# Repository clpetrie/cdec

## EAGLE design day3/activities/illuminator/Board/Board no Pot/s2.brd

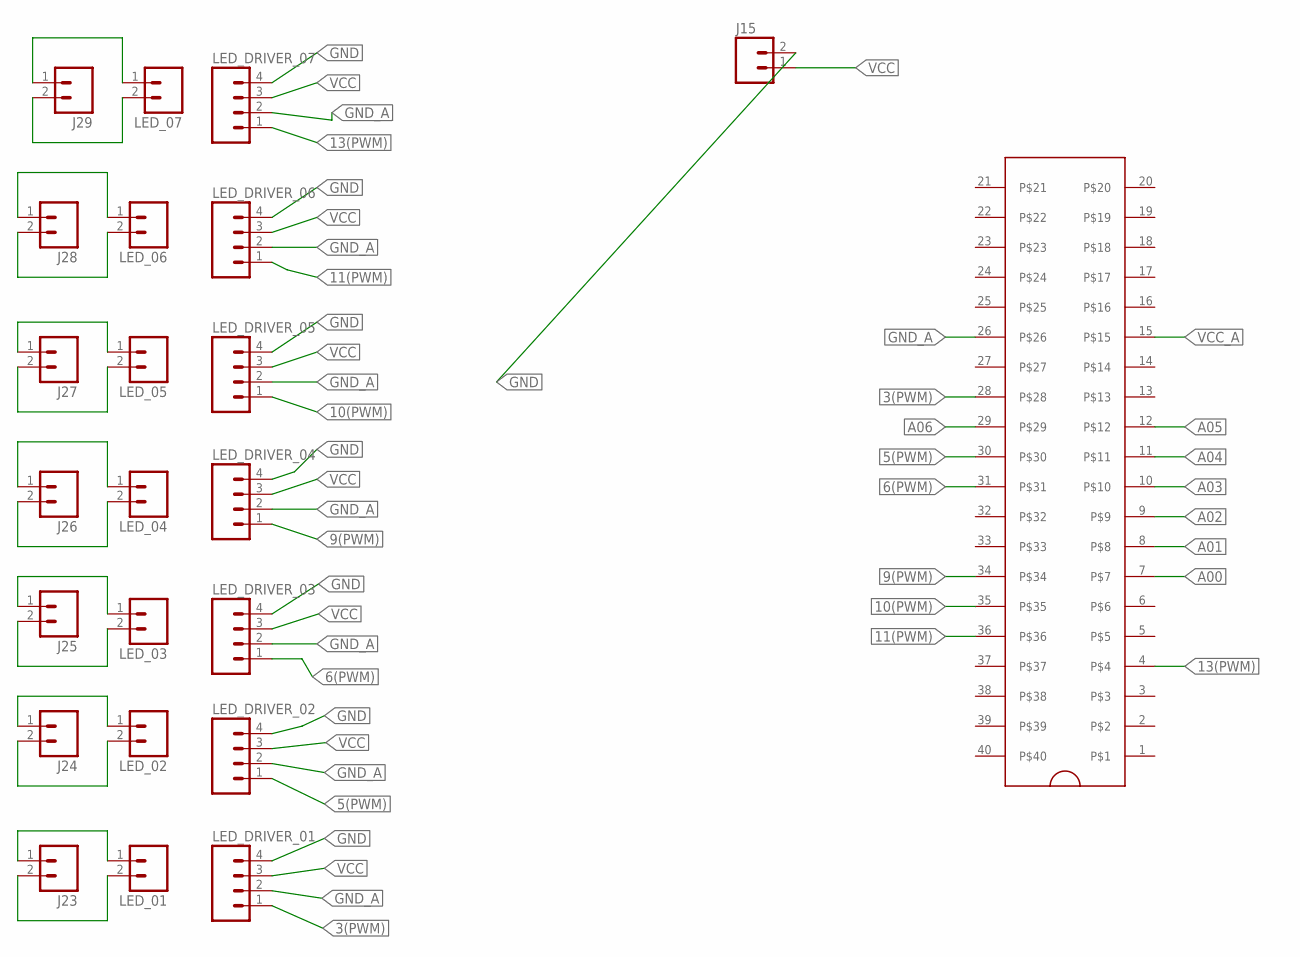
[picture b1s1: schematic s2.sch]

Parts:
ARDUINO_MICRO: ZIFSOCKET-40-6DIL40-6-ZIF_SOCKET; DIL40-6-ZIF_SOCKET
J15, J23, J24, J25, J26, J27, J28, J29: M02PTH; 1X02
LED_01, LED_02, LED_03, LED_04, LED_05, LED_06, LED_07: M02PTH; 1X02
LED_DRIVER_01, LED_DRIVER_02, LED_DRIVER_03, LED_DRIVER_04, LED_DRIVER_05, LED_DRIVER_06, LED_DRIVER_07: M04PTH; 1X04

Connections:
3(PWM): ARDUINO_MICRO.28, LED_DRIVER_01.1
5(PWM): ARDUINO_MICRO.30, LED_DRIVER_02.1
6(PWM): ARDUINO_MICRO.31, LED_DRIVER_03.1
9(PWM): ARDUINO_MICRO.34, LED_DRIVER_04.1
10(PWM): ARDUINO_MICRO.35, LED_DRIVER_05.1
11(PWM): ARDUINO_MICRO.36, LED_DRIVER_06.1
13(PWM): ARDUINO_MICRO.4, LED_DRIVER_07.1
A00: ARDUINO_MICRO.7
A01: ARDUINO_MICRO.8
A02: ARDUINO_MICRO.9
A03: ARDUINO_MICRO.10
A04: ARDUINO_MICRO.11
A05: ARDUINO_MICRO.12
A06: ARDUINO_MICRO.29
GND: J15.2, LED_DRIVER_01.4, LED_DRIVER_02.4, LED_DRIVER_03.4, LED_DRIVER_04.4, LED_DRIVER_05.4, LED_DRIVER_06.4, LED_DRIVER_07.4
GND_A: ARDUINO_MICRO.26, LED_DRIVER_01.2, LED_DRIVER_02.2, LED_DRIVER_03.2, LED_DRIVER_04.2, LED_DRIVER_05.2, LED_DRIVER_06.2, LED_DRIVER_07.2
unnamed: J23.1, LED_01.1
unnamed: J23.2, LED_01.2
unnamed: J24.2, LED_02.2
unnamed: J24.1, LED_02.1
unnamed: J25.2, LED_03.2
unnamed: J25.1, LED_03.1
unnamed: J26.2, LED_04.2
unnamed: J26.1, LED_04.1
unnamed: J27.2, LED_05.2
unnamed: J27.1, LED_05.1
unnamed: J28.2, LED_06.2
unnamed: J28.1, LED_06.1
unnamed: J29.2, LED_07.2
unnamed: J29.1, LED_07.1
VCC: J15.1, LED_DRIVER_01.3, LED_DRIVER_02.3, LED_DRIVER_03.3, LED_DRIVER_04.3, LED_DRIVER_05.3, LED_DRIVER_06.3, LED_DRIVER_07.3
VCC_A: ARDUINO_MICRO.15

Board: 2 copper layers, 23 parts (23 on the bottom side), 24 nets, no tracks yet.

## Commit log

2017-07-30 Added files for day1 only to test things.
2017-07-30 Added files for most other days.
2017-07-31 Added fix for import issue in anaconda.
2017-07-31 Fixed the fix for the "import" issue.
2017-08-01 Testing the .gitignore file.
2017-08-01 Another change to .gitignore.
2017-08-01 testing
2017-08-01 Fixed .gitignore problems... I think.
2017-08-01 Added day 2 presentation from David.

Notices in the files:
parts and their libraries:
SparkFun-Connectors: Licensing: Creative Commons ShareAlike 4.0 International - https://creativecommons.org/licenses/by-sa/4.0
